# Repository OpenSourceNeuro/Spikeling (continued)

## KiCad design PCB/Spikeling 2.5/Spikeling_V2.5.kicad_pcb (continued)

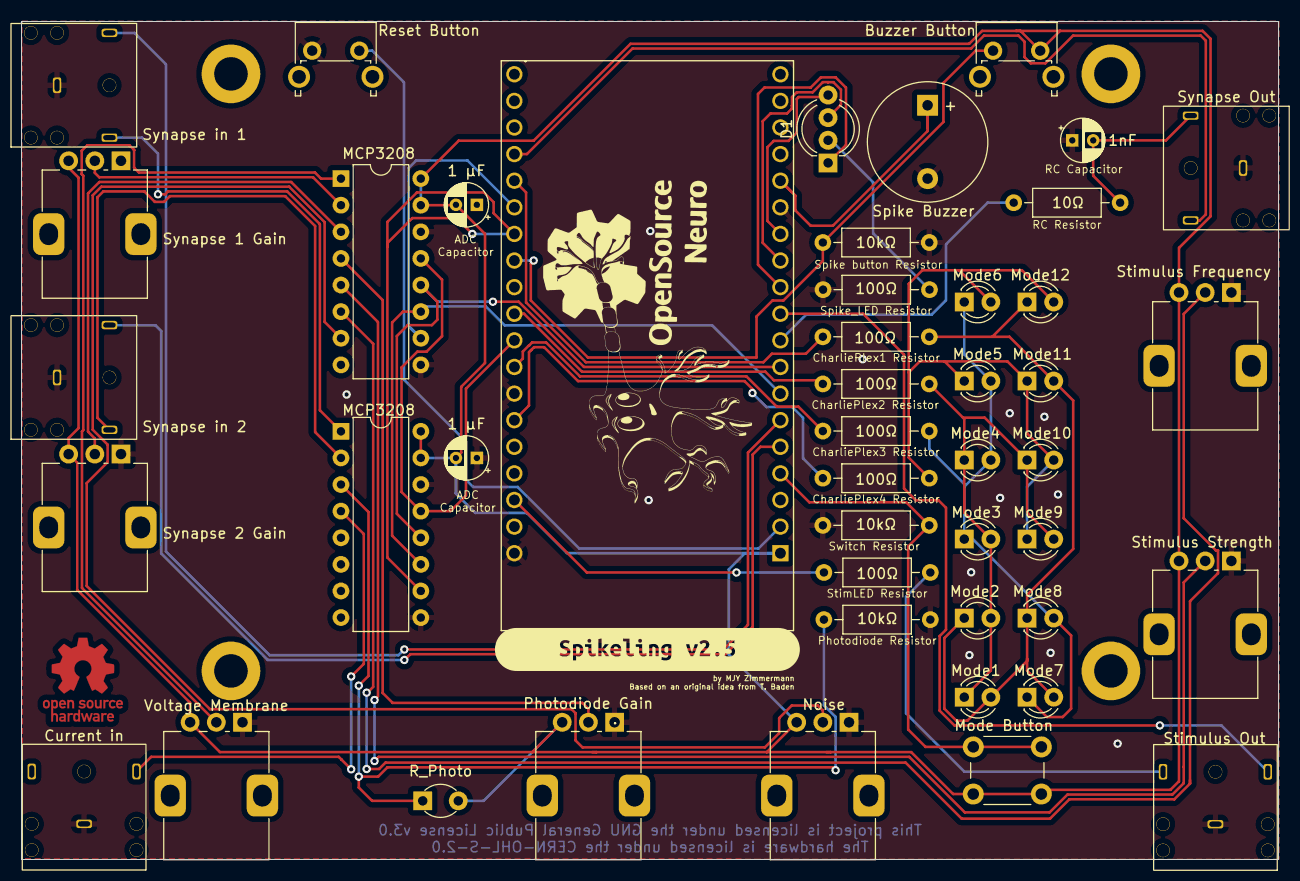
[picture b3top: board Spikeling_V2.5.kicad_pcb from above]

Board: 2 copper layers, 120.0 x 80.0 mm, 53 parts (0 on the bottom side), 42 nets.

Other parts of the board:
 : MountingHole_3.2mm_M3_DIN965_Pad
 #2: MountingHole_M3; MountingHole_3.2mm_M3_DIN965_Pad
 #3,  #4: MountingHole_3.2mm_M3_DIN965_Pad
.: Spikeling_neuron; Spikeling_Photoreceptor
.#2: Spikeling_neuron; Spikeling_Neuron
kibuzzard-6957C1B9: G***; kibuzzard-6957C1B9

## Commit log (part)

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2025-08-31 update Arduino
2025-08-31 update PyQt
2025-10-16 first steps for comversion of very long readme to full mkdoc documentation
2025-10-16 add versioning of the docs with package mike, will need to run git commands to link it to git versioning when full doc
2025-10-16 break down of large readme into a structured mkdocs directory tree, WIP
2025-11-20 update PCB
2025-12-08 commit archives
2025-12-08 update GUI
2025-12-08 update docs
2025-12-23 first commit android app
2025-12-23 Update archives
2025-12-23 update images
2025-12-29 Deployed e5e1c24 to 2.2 with MkDocs 1.6.1 and mike 2.1.3
2025-12-29 upload docs
2025-12-29 Deployed 46b8dca to 2.2 with MkDocs 1.6.1 and mike 2.1.3
2025-12-29 Set default version to latest with mike 2.1.3
2025-12-29 upload site
2025-12-29 Deployed 0255721 to 3.0.1 with MkDocs 1.6.1 and mike 2.1.3
2026-01-02 update site
2026-01-02 update venv
2026-01-02 upload licenses
2026-01-03 restructure software folder
2026-01-03 update virtual environment for mkdocs
2026-01-03 restructure archive folder
2026-01-03 restructure documentation folder
2026-01-03 restructure Firmware folder
2026-01-03 update firmware folder
2026-01-03 restructure hardware folder
2026-01-03 remove instruction manual
2026-01-03 Main project License - GPL v3
2026-01-04 update Documentation
2026-01-04 update Images folder
2026-01-06 update Firmware
2026-01-06 update Hardware
2026-01-06 update Software
2026-02-17 update design
2026-02-23 declassify version 3.1
2026-03-10 update recording files
2026-03-11 update Software includes tetrode
2026-03-11 update ui
2026-03-12 Update Software, includes new tetrode window
2026-03-13 update software tetrode view fix
2026-03-13 update software tetrode rotation fixed
2026-05-26 update arduino files v3
2026-06-03 update version2.5 firmware
